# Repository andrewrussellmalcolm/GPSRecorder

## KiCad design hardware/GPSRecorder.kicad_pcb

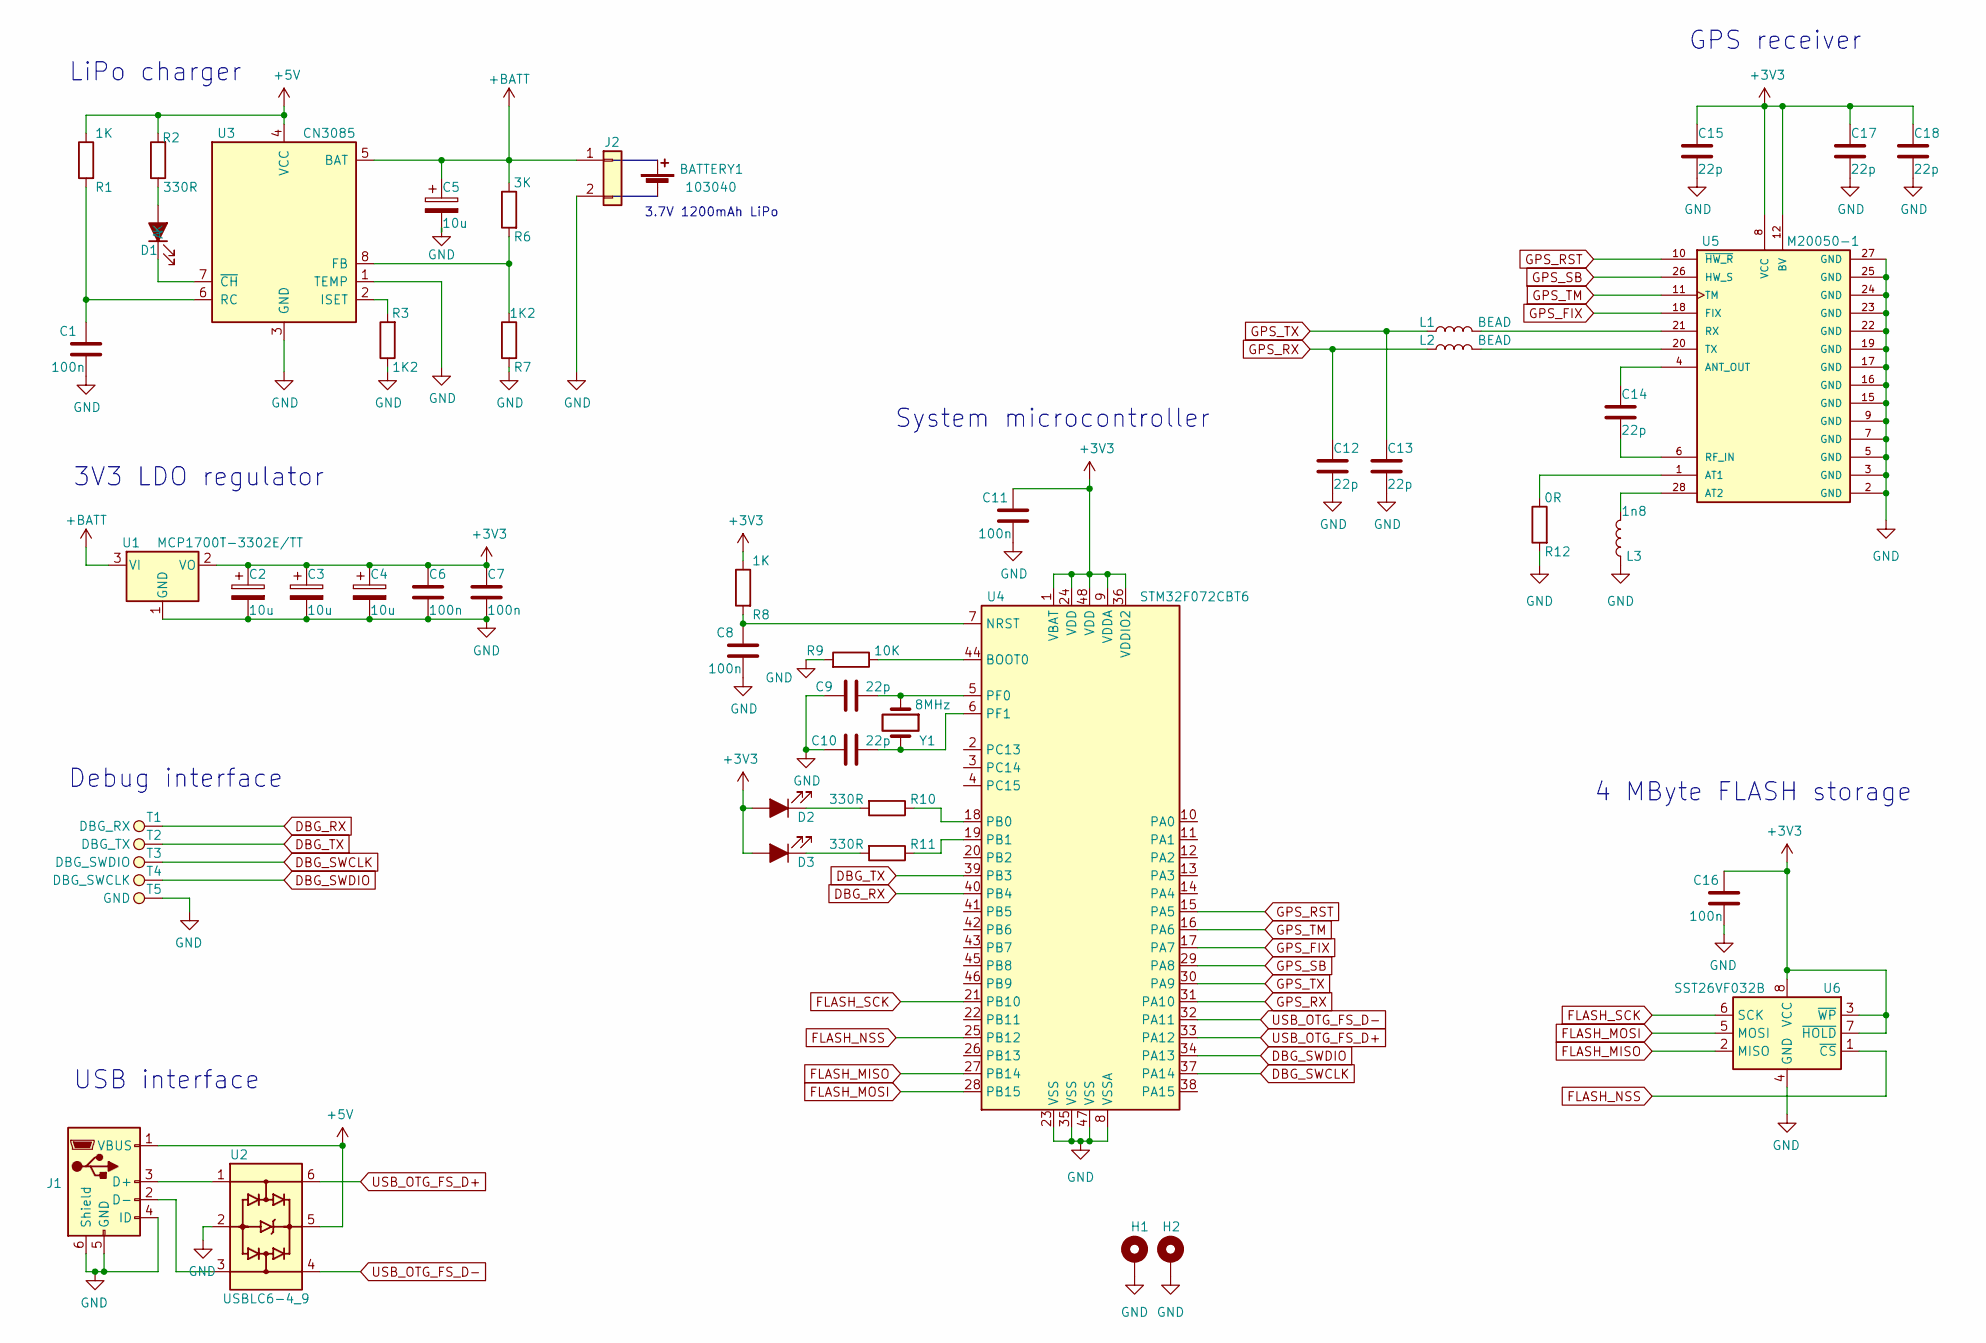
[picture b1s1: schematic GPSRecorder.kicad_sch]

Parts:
BATTERY1: 103040; dummy; Voltage 3; PartNo 97384022
C1, C8, C11, C16: 100n; C_0603_1608Metric; Voltage 50V; PartNo C0603C104K4RACTU
C2, C3, C4, C5: 10u; CP_EIA-3216-10_Kemet-I
C6, C7: 100n; C_0603_1608Metric
C9, C10: 22p; C_0603_1608Metric; Voltage 50V; PartNo C0603C220J5GACTU
C12, C13, C14, C15, C17, C18: 22p; C_0603_1608Metric; Voltage 50V; PartNo C0603C101J5GACTU
D1: LTST-C190KRKT; LED_0603_1608Metric
D2, D3: LED_RED; LED_0603_1608Metric; PartNo LS Q976
H1, H2: MountingHole_Pad; MountingHole_2.2mm_M2_Pad
J1: USB_OTG; USB_Micro-B_Molex_47346-0001; PartNo 105133-0011
J2: Conn_01x02; JST_PH_B2B-PH-K_1x02_P2.00mm_Vertical
L1, L2: BEAD; L_0603_1608Metric; PartNo LQW18AN2N2D00D
L3: 1n8; L_0603_1608Metric; PartNo LQW18AN2N2D00D
R1, R8: 1K; R_0603_1608Metric; PartNo CRG0603F1K
R2: 330R; R_0603_1608Metric
R3: 1K2; R_0603_1608Metric
R6: 3K; R_0603_1608Metric; PartNo CRG0603F1K
R7: 1K2; R_0603_1608Metric; PartNo CRG0603F1K
R9: 10K; R_0603_1608Metric; PartNo CRG0603F10K
R10, R11: 330R; R_0603_1608Metric; PartNo CRG0603F330R
R12: 0R; R_0603_1608Metric; PartNo CRG0603F10K
T1: DBG_RX; TestPoint_Pad_D2.0mm
T2: DBG_TX; TestPoint_Pad_D2.0mm
T3: DBG_SWDIO; TestPoint_Pad_D2.0mm
T4: DBG_SWCLK; TestPoint_Pad_D2.0mm
T5: GND; TestPoint_Pad_D2.0mm
U1: MCP1700T-3302E/TT; SOT-23
U2: USBLC6-4_9; SOT-23-6; PartNo USBLC6-2SC6Y
U3: CN3085; SOIC-8-1EP_3.9x4.9mm_P1.27mm_EP2.29x3mm
U4: STM32F072CBT6; LQFP-48_7x7mm_P0.5mm
U5: M20050-1; XCVR_M20050-1; PARTREV M20050-1-PS-2.01
U6: SST26VF032B; SOIC-8_5.275x5.275mm_P1.27mm; PartNo SST26VF032B-104I/SM
Y1: 8MHz; Crystal_SMD_Abracon_ABM8AIG-4Pin_3.2x2.5mm; PartNo ABM8AIG-8.000MHZ-8-V1R-T

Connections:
+3V3: C2.1, C3.1, C4.1, C6.1, C7.1, C11.2, C15.1, C16.2, C17.1, C18.1, D2.2 (A), D3.2 (A), R8.1, U1.2 (VO), U4.1 (VBAT), U4.9 (VDDA), U4.24 (VDD), U4.36 (VDDIO2), U4.48 (VDD), U5.8 (VCC), U5.12 (BV), U6.3 (~WP), U6.7 (~HOLD), U6.8 (VCC)
+5V: J1.1 (VBUS), R1.1, R2.2, U2.5, U3.4 (VCC)
+BATT: C5.1, J2.1, R6.1, U1.3 (VI), U3.5 (BAT)
DBG_RX: T1.1, U4.40 (PB4)
DBG_SWCLK: T3.1, U4.37 (PA14)
DBG_SWDIO: T4.1, U4.34 (PA13)
DBG_TX: T2.1, U4.39 (PB3)
FLASH_MISO: U4.27 (PB14), U6.2 (MISO)
FLASH_MOSI: U4.28 (PB15), U6.5 (MOSI)
FLASH_NSS: U4.25 (PB12), U6.1 (~CS)
FLASH_SCK: U4.21 (PB10), U6.6 (SCK)
GND: C1.1, C2.2, C3.2, C4.2, C5.2, C6.2, C7.2, C8.1, C9.2, C10.2, C11.1, C12.2, C13.2, C15.2, C16.1, C17.2, C18.2, H1.1, H2.1, J1.4 (ID), J1.5 (GND), J1.6 (Shield), J2.2, L3.1, R3.1, R7.2, R9.2, R12.2, T5.1, U1.1 (GND), U2.2, U3.1 (TEMP), U3.3 (GND), U4.8 (VSSA), U4.23 (VSS), U4.35 (VSS), U4.47 (VSS), U5.2 (GND), U5.3 (GND), U5.5 (GND), U5.7 (GND), U5.9 (GND), U5.15 (GND), U5.16 (GND), U5.17 (GND), U5.19 (GND), U5.22 (GND), U5.23 (GND), U5.24 (GND), U5.25 (GND), U5.27 (GND), U6.4 (GND)
GPS_FIX: U4.17 (PA7), U5.18 (FIX)
GPS_RST: U4.15 (PA5), U5.10 (~HW_R)
GPS_RX: C12.1, L2.1, U4.31 (PA10)
GPS_SB: U4.29 (PA8), U5.26 (HW_S)
GPS_TM: U4.16 (PA6), U5.11 (TM)
GPS_TX: C13.1, L1.1, U4.30 (PA9)
unnamed: C1.2, R1.2, U3.6 (RC)
unnamed: C8.2, R8.2, U4.7 (NRST)
unnamed: C9.1, U4.5 (PF0), Y1.1
unnamed: C10.1, U4.6 (PF1), Y1.3
unnamed: C14.1, U5.4 (ANT_OUT)
unnamed: C14.2, U5.6 (RF_IN)
unnamed: D1.1 (K), U3.7 (~CH)
unnamed: D1.2 (A), R2.1
unnamed: D2.1 (K), R10.2
unnamed: D3.1 (K), R11.2
unnamed: J1.2 (D-), U2.3
unnamed: J1.3 (D+), U2.1
unnamed: L1.2, U5.21 (RX)
unnamed: L2.2, U5.20 (TX)
unnamed: L3.2, U5.28 (AT2)
unnamed: R3.2, U3.2 (ISET)
unnamed: R6.2, R7.1, U3.8 (FB)
unnamed: R9.1, U4.44 (BOOT0)
unnamed: R10.1, U4.18 (PB0)
unnamed: R11.1, U4.19 (PB1)
unnamed: R12.1, U5.1 (AT1)
USB_OTG_FS_D+: U2.6, U4.33 (PA12)
USB_OTG_FS_D-: U2.4, U4.32 (PA11)

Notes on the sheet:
3V3 LDO regulator
LiPo charger
USB interface
4 MByte FLASH storage
System microcontroller
Debug interface
GPS receiver
3.7V 1200mAh LiPo

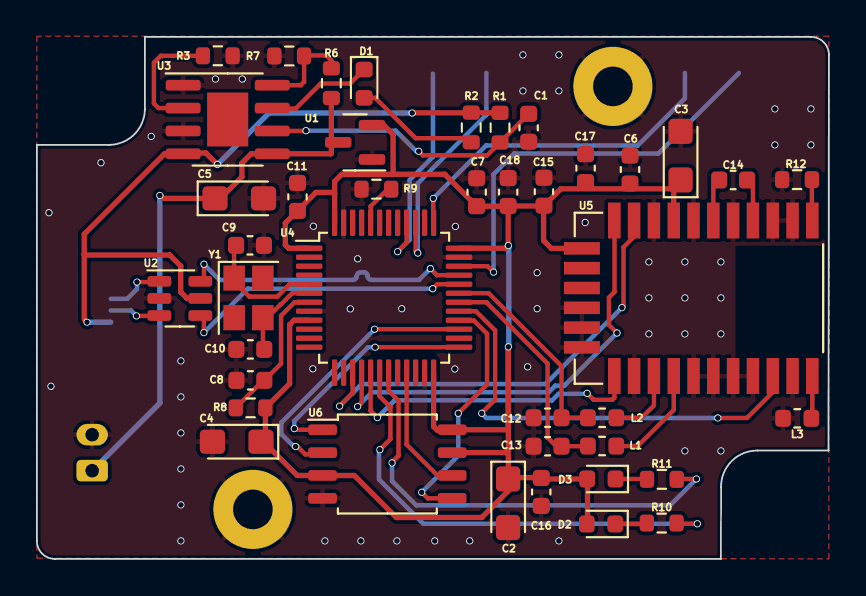
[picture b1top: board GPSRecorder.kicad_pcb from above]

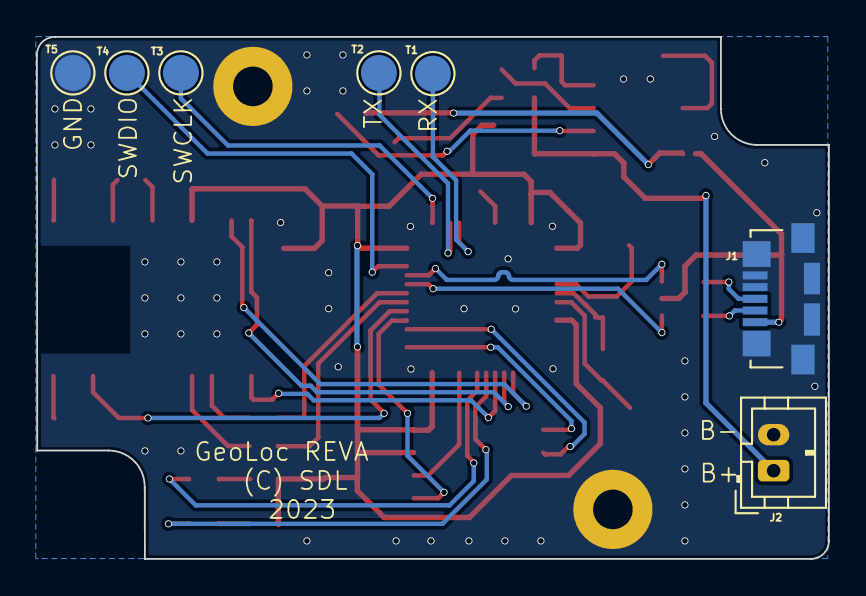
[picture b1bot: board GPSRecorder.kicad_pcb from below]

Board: 2 copper layers, 44.0 x 29.0 mm, 51 parts (8 on the bottom side), 41 nets.

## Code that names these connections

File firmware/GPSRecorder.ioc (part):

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Mcu.Name=STM32F072C(8-B)Tx
Mcu.Package=LQFP48
Mcu.UserName=STM32F072CBTx
PA10.GPIOParameters=GPIO_Label
PA10.GPIO_Label=GPS_RX
PA10.Mode=Asynchronous
PA10.Signal=USART1_RX
PA11.Mode=Device
PA11.Signal=USB_DM
PA12.Mode=Device
PA12.Signal=USB_DP
PA13.Mode=Serial_Wire
PA13.Signal=SYS_SWDIO
PA14.Mode=Serial_Wire
PA14.Signal=SYS_SWCLK
PA5.GPIOParameters=PinState,GPIO_Label
PA5.GPIO_Label=GPS_RST
PA5.PinState=GPIO_PIN_RESET
PA5.Signal=GPIO_Output
PA6.GPIOParameters=GPIO_Label
PA6.GPIO_Label=GPS_TM
PA6.Signal=GPIO_Input
PA7.GPIOParameters=GPIO_Label
PA7.GPIO_Label=GPS_FIX
PA7.Signal=GPIO_Input
PA8.GPIOParameters=PinState,GPIO_Label
PA8.GPIO_Label=GPS_SB
PA8.PinState=GPIO_PIN_SET
PA8.Signal=GPIO_Output
PA9.GPIOParameters=GPIO_Label
PA9.GPIO_Label=GPS_TX
PA9.Mode=Asynchronous
PA9.Signal=USART1_TX
PB0.GPIOParameters=PinState,GPIO_Label
PB0.GPIO_Label=LED0
PB0.PinState=GPIO_PIN_SET
PB0.Signal=GPIO_Output
PB1.GPIOParameters=PinState,GPIO_Label
PB1.GPIO_Label=LED1
PB1.PinState=GPIO_PIN_SET
PB1.Signal=GPIO_Output
PB10.GPIOParameters=GPIO_Label
PB10.GPIO_Label=FLASH_SCK
PB10.Mode=Full_Duplex_Master
PB10.Signal=SPI2_SCK
PB12.GPIOParameters=PinState,GPIO_Label
PB12.GPIO_Label=FLASH_NSS
PB12.PinState=GPIO_PIN_SET
PB12.Signal=GPIO_Output
PB14.GPIOParameters=GPIO_Label
PB14.GPIO_Label=FLASH_MISO
PB14.Mode=Full_Duplex_Master
PB14.Signal=SPI2_MISO
PB15.GPIOParameters=GPIO_Label
PB15.GPIO_Label=FLASH_MOSI
PB15.Mode=Full_Duplex_Master
PB15.Signal=SPI2_MOSI
PF0-OSC_IN.Mode=HSE-External-Oscillator
PF0-OSC_IN.Signal=RCC_OSC_IN
PF1-OSC_OUT.Mode=HSE-External-Oscillator
PF1-OSC_OUT.Signal=RCC_OSC_OUT
RCC.SYSCLKFreq_VALUE=48000000
RCC.SYSCLKSource=RCC_SYSCLKSOURCE_PLLCLK
board=custom
